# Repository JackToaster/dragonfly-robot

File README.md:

# Dragonfly Robot
This repository contains hardware and firmware files for a flight controller & 4-channel servo driver, intended for my dragonfly ornithopter robot.

## Robot hardware
The robot is built from components 3d printed out of lightweight PLA and pulltruded carbon fiber rods, with two standard 3.7g RC servos actuating each wing.

## PCB
The flight controlelr hardware is based on the WCH CH32V203, a low-cost RISC-V microcontroller.
Motor drives use the TI DRV8212 full-bridge driver and INA199 current sense amplifier for current feedback.
Each controller drives one pair of wings (four actuators). The controllers for each wing pair communicate with each other via I2C. An I2C IMU (MPU6050/MPU9250) is used for attitude control, and an RC receiver is connected over a serial link via the CRSF protocol.

## Firmware
The firmware in this repository utilizes CNLohr's [CH32Fun](https://github.com/cnlohr/ch32fun) framework for register mapping and hardware initialization functionality.

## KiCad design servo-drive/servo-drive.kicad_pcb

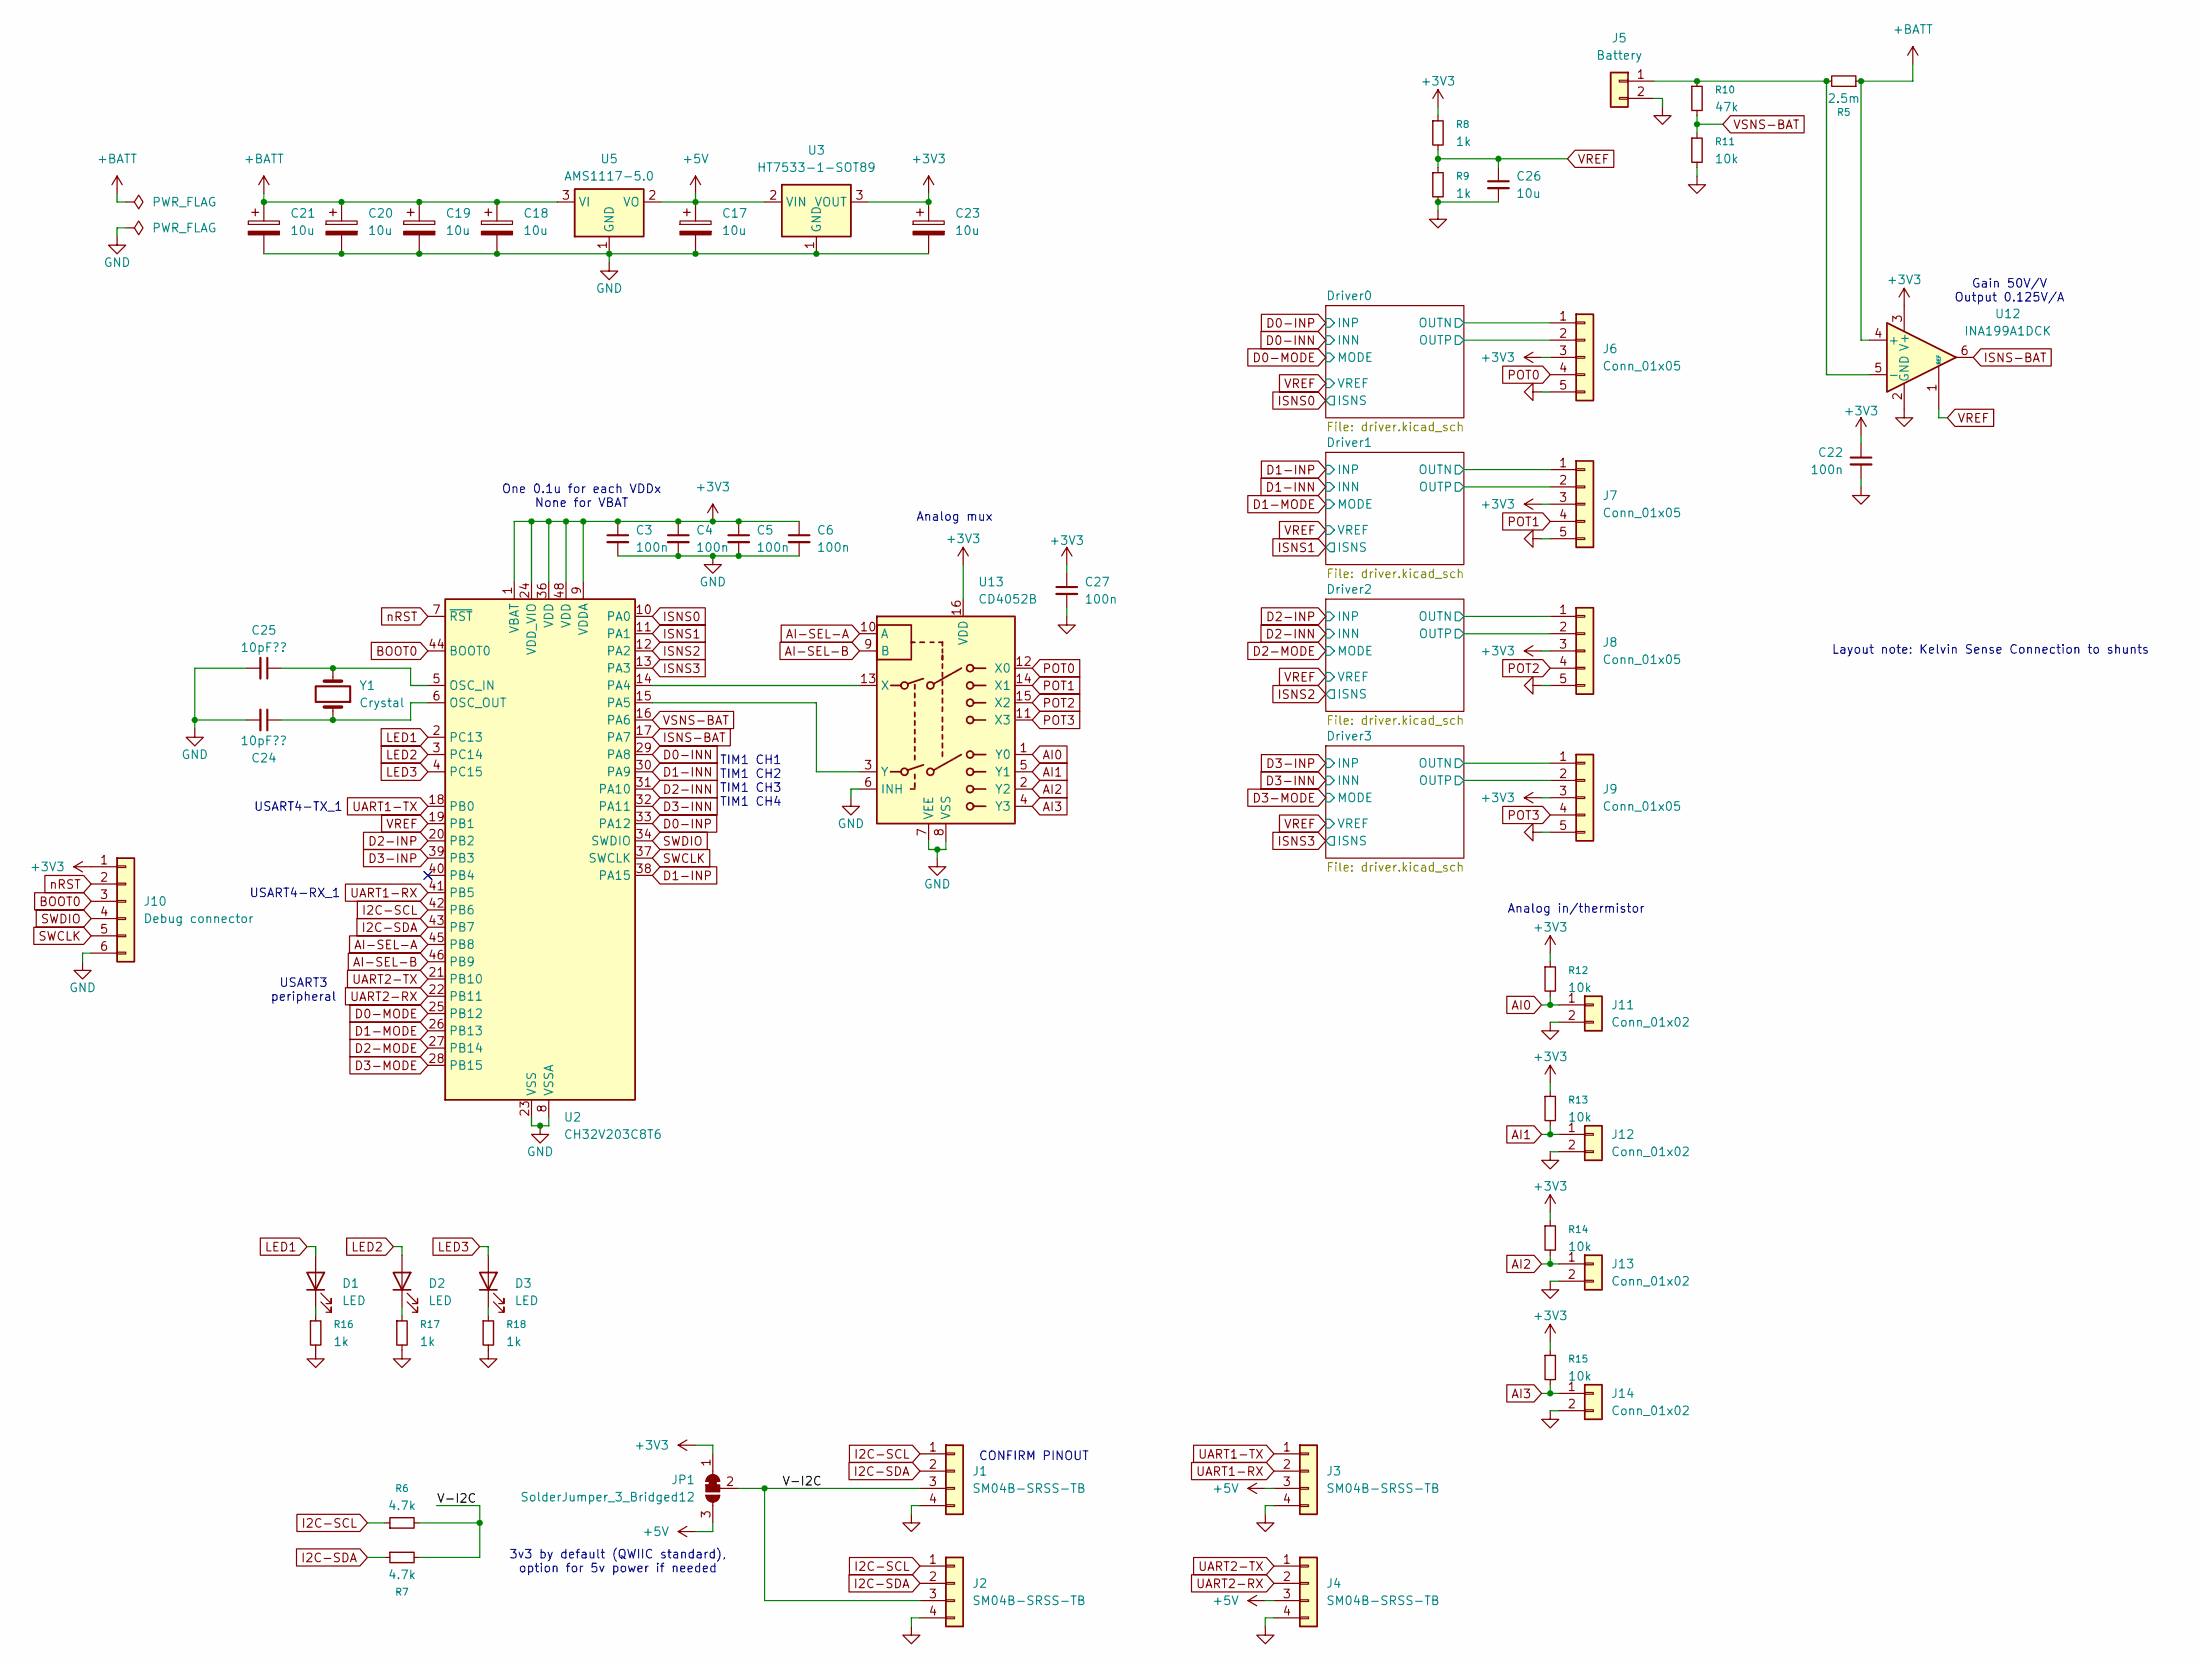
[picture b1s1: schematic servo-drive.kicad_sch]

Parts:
C3, C4, C5, C6, C22, C27: 100n; C_0402_1005Metric; LCSC C307331
C17, C18, C19, C20, C21, C23: 10u; CP_EIA-3216-18_Kemet-A; LCSC C7171
C24, C25: 10pF??; C_0402_1005Metric; LCSC C32949
C26: 10u; C_0603_1608Metric; LCSC C19702
D1, D2, D3: LED; LED_0603_1608Metric_Pad1.05x0.95mm_HandSolder
J1, J2, J3, J4: SM04B-SRSS-TB; JST_ZH_B4B-ZR_1x04_P1.50mm_Vertical
J5: Battery; SolderWire-1sqmm_1x02_P7.8mm_D1.4mm_OD3.9mm
J6, J7, J8, J9: Conn_01x05; JST_ZH_B5B-ZR_1x05_P1.50mm_Vertical
J10: Debug connector; PinHeader_1x06_P1.27mm_Vertical
J11, J12, J13, J14: Conn_01x02; JST_ZH_B2B-ZR_1x02_P1.50mm_Vertical
JP1: SolderJumper_3_Bridged12; SolderJumper-3_P1.3mm_Bridged12_RoundedPad1.0x1.5mm
R5: 2.5m; R_0805_2012Metric; LCSC C728266
R6, R7: 4.7k; R_0402_1005Metric; LCSC C25900
R8, R9, R16, R17, R18: 1k; R_0402_1005Metric; LCSC C11702
R10: 47k; R_0402_1005Metric; LCSC C25792
R11, R12, R13, R14, R15: 10k; R_0402_1005Metric; LCSC C25744
U2: CH32V203C8T6; LQFP-48_7x7mm_P0.5mm; LCSC C3001172
U3: HT7533-1-SOT89; SOT-89-3; LCSC C14289
U5: AMS1117-5.0; SOT-223-3_TabPin2; LCSC C6187
U12: INA199A1DCK; SOT-363_SC-70-6; LCSC C2653849
U13: CD4052B; SOIC-16_3.9x9.9mm_P1.27mm; LCSC C6521
Y1: Crystal; Crystal_SMD_5032-2Pin_5.0x3.2mm; LCSC C115962

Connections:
+3V3: C3.1, C4.1, C5.1, C6.1, C22.1, C23.1, C27.1, J6.3, J7.3, J8.3, J9.3, J10.1, JP1.1 (A), R8.1, R12.1, R13.1, R14.1, R15.1, U2.1 (VBAT), U2.9 (VDDA), U2.24 (VDD_VIO), U2.36 (VDD), U2.48 (VDD), U3.3 (VOUT), U12.3 (V+), U13.16 (VDD); also elsewhere on the board
+5V: C17.1, J3.3, J4.3, JP1.3 (B), U3.2 (VIN), U5.2 (VO)
+BATT: C18.1, C19.1, C20.1, C21.1, R5.1, U5.3 (VI), U12.4 (+); also elsewhere on the board
/Driver0/OUTN: J6.1; also elsewhere on the board
/Driver0/OUTP: J6.2; also elsewhere on the board
/Driver1/OUTN: J7.1; also elsewhere on the board
/Driver1/OUTP: J7.2; also elsewhere on the board
/Driver2/OUTN: J8.1; also elsewhere on the board
/Driver2/OUTP: J8.2; also elsewhere on the board
/Driver3/OUTN: J9.1; also elsewhere on the board
/Driver3/OUTP: J9.2; also elsewhere on the board
/V-I2C: J1.3, J2.3, JP1.2 (C), R6.2, R7.2
AI0: J11.1, R12.2, U13.1 (Y0)
AI1: J12.1, R13.2, U13.5 (Y1)
AI2: J13.1, R14.2, U13.2 (Y2)
AI3: J14.1, R15.2, U13.4 (Y3)
AI-SEL-A: U2.45 (PB8), U13.10 (A)
AI-SEL-B: U2.46 (PB9), U13.9 (B)
BOOT0: J10.3, U2.44 (BOOT0)
D0-INN: U2.29 (PA8); also elsewhere on the board
D0-INP: U2.33 (PA12); also elsewhere on the board
D0-MODE: U2.25 (PB12); also elsewhere on the board
D1-INN: U2.30 (PA9); also elsewhere on the board
D1-INP: U2.38 (PA15); also elsewhere on the board
D1-MODE: U2.26 (PB13); also elsewhere on the board
D2-INN: U2.31 (PA10); also elsewhere on the board
D2-INP: U2.20 (PB2); also elsewhere on the board
D2-MODE: U2.27 (PB14); also elsewhere on the board
D3-INN: U2.32 (PA11); also elsewhere on the board
D3-INP: U2.39 (PB3); also elsewhere on the board
D3-MODE: U2.28 (PB15); also elsewhere on the board
GND: C3.2, C4.2, C5.2, C6.2, C17.2, C18.2, C19.2, C20.2, C21.2, C22.2, C23.2, C24.2, C25.2, C26.2, C27.2, J1.4, J2.4, J3.4, J4.4, J5.2, J6.5, J7.5, J8.5, J9.5, J10.6, J11.2, J12.2, J13.2, J14.2, R9.2, R11.2, R16.2, R17.2, R18.2, U2.8 (VSSA), U2.23 (VSS), U2.35 (VSS), U2.47 (VSS), U3.1 (GND), U5.1 (GND), U12.2 (GND), U13.6 (INH), U13.7 (VEE), U13.8 (VSS); also elsewhere on the board
I2C-SCL: J1.1, J2.1, R6.1, U2.42 (PB6)
I2C-SDA: J1.2, J2.2, R7.1, U2.43 (PB7)
ISNS0: U2.10 (PA0); also elsewhere on the board
ISNS1: U2.11 (PA1); also elsewhere on the board
ISNS2: U2.12 (PA2); also elsewhere on the board
ISNS3: U2.13 (PA3); also elsewhere on the board
ISNS-BAT: U2.17 (PA7), U12.6
LED1: D1.2 (A), U2.2 (PC13)
LED2: D2.2 (A), U2.3 (PC14)
LED3: D3.2 (A), U2.4 (PC15)
unnamed: D1.1 (K), R16.1
unnamed: D2.1 (K), R17.1
unnamed: D3.1 (K), R18.1
unnamed: J5.1, R5.2, R10.1, U12.5 (-)
unnamed: C25.1, U2.5 (OSC_IN), Y1.2
unnamed: C24.1, U2.6 (OSC_OUT), Y1.1
unnamed: U2.14 (PA4), U13.13 (X)
unnamed: U2.15 (PA5), U13.3 (Y)
POT0: J6.4, U13.12 (X0)
POT1: J7.4, U13.14 (X1)
POT2: J8.4, U13.15 (X2)
POT3: J9.4, U13.11 (X3)
SWCLK: J10.5, U2.37 (SWCLK)
SWDIO: J10.4, U2.34 (SWDIO)
UART1-RX: J3.2, U2.41 (PB5)
UART1-TX: J3.1, U2.18 (PB0)
UART2-RX: J4.2, U2.22 (PB11)
UART2-TX: J4.1, U2.21 (PB10)
VREF: C26.1, R8.2, R9.1, U2.19 (PB1), U12.1 (REF); also elsewhere on the board
VSNS-BAT: R10.2, R11.1, U2.16 (PA6)
nRST: J10.2, U2.7 (~RST)

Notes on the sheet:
Analog mux
USART4-TX_1
Analog in/thermistor
USART4-RX_1
Gain 50V/V Output 0.125V/A
Layout note: Kelvin Sense Connection to shunts
CONFIRM PINOUT
One 0.1u for each VDDx None for VBAT
3v3 by default (QWIIC standard), option for 5v power if needed
USART3 peripheral
TIM1 CH1 TIM1 CH2 TIM1 CH3 TIM1 CH4

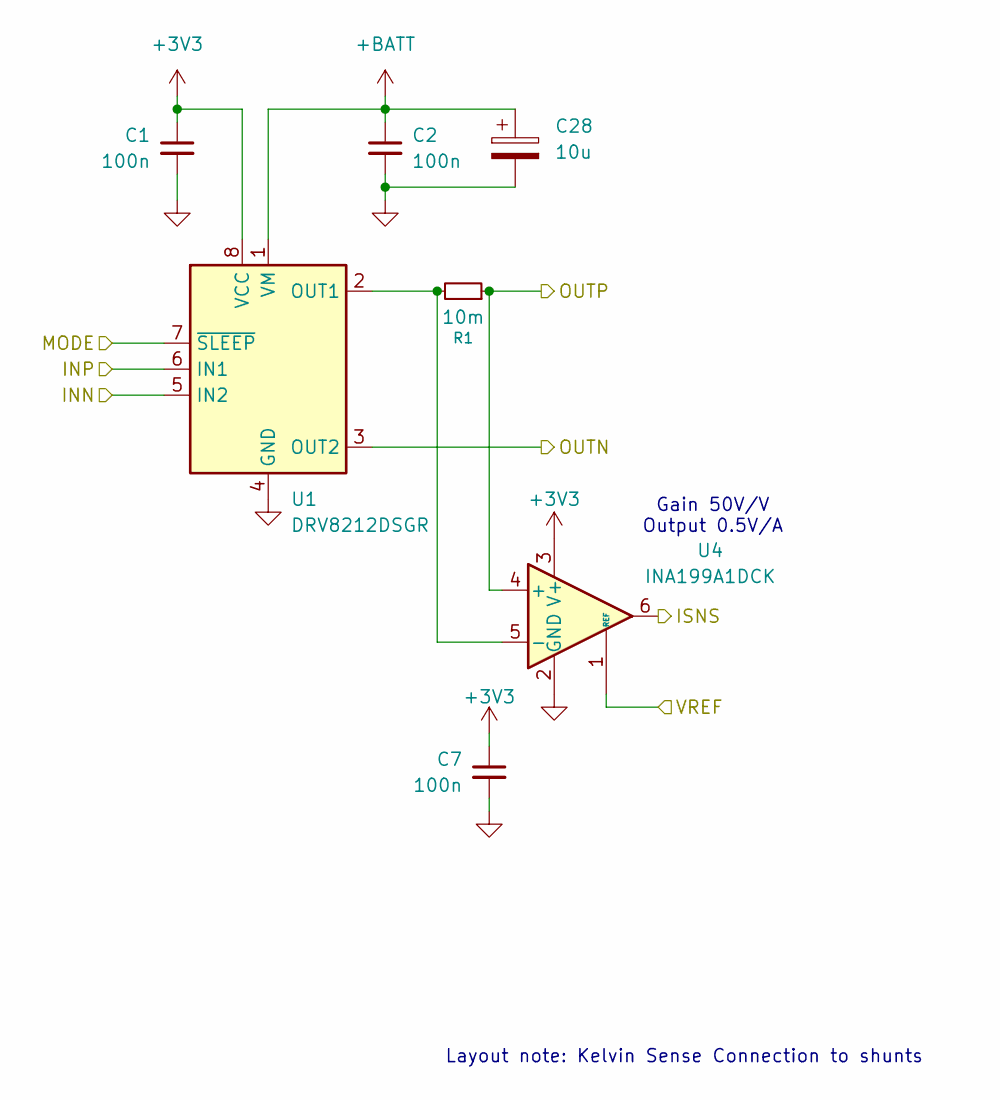
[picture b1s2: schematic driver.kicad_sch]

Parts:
C1, C2, C7: 100n; C_0402_1005Metric; LCSC C307331
C28: 10u; CP_EIA-3216-18_Kemet-A; LCSC C7171
R1: 10m; R_0805_2012Metric; LCSC C104574
U1: DRV8212DSGR; WSON-8-1EP_2x2mm_P0.5mm_EP0.9x1.6mm_ThermalVias; LCSC C2843766
U4: INA199A1DCK; SOT-363_SC-70-6; LCSC C2653849

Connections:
+3V3: C1.1, C7.1, U1.8 (VCC), U4.3 (V+); also elsewhere on the board
+BATT: C2.1, C28.1, U1.1 (VM); also elsewhere on the board
/Driver0/OUTN: U1.3 (OUT2); also elsewhere on the board
/Driver0/OUTP: R1.1, U4.4 (+); also elsewhere on the board
D0-INN: U1.5 (IN2); also elsewhere on the board
D0-INP: U1.6 (IN1); also elsewhere on the board
D0-MODE: U1.7 (~SLEEP); also elsewhere on the board
GND: C1.2, C2.2, C7.2, C28.2, U1.4 (GND), U1.9 (GND), U4.2 (GND); also elsewhere on the board
ISNS0: U4.6; also elsewhere on the board
unnamed: R1.2, U1.2 (OUT1), U4.5 (-)
VREF: U4.1 (REF); also elsewhere on the board

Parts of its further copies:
C8, C9, C10, C11, C12, C13, C14, C15, C16: 100n; C_0402_1005Metric; LCSC C307331
C29, C30, C31: 10u; CP_EIA-3216-18_Kemet-A; LCSC C7171
R2, R3, R4: 10m; R_0805_2012Metric; LCSC C104574
U6, U8, U10: DRV8212DSGR; WSON-8-1EP_2x2mm_P0.5mm_EP0.9x1.6mm_ThermalVias; LCSC C2843766
U7, U9, U11: INA199A1DCK; SOT-363_SC-70-6; LCSC C2653849

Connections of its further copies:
+3V3: C8.1, C10.1, C11.1, C13.1, C14.1, C16.1, U6.8 (VCC), U7.3 (V+), U8.8 (VCC), U9.3 (V+), U10.8 (VCC), U11.3 (V+); also elsewhere on the board
+BATT: C9.1, C12.1, C15.1, C29.1, C30.1, C31.1, U6.1 (VM), U8.1 (VM), U10.1 (VM); also elsewhere on the board
/Driver1/OUTN: U6.3 (OUT2); also elsewhere on the board
/Driver1/OUTP: R2.1, U7.4 (+); also elsewhere on the board
/Driver2/OUTN: U8.3 (OUT2); also elsewhere on the board
/Driver2/OUTP: R3.1, U9.4 (+); also elsewhere on the board
/Driver3/OUTN: U10.3 (OUT2); also elsewhere on the board
/Driver3/OUTP: R4.1, U11.4 (+); also elsewhere on the board
D1-INN: U6.5 (IN2); also elsewhere on the board
D1-INP: U6.6 (IN1); also elsewhere on the board
D1-MODE: U6.7 (~SLEEP); also elsewhere on the board
D2-INN: U8.5 (IN2); also elsewhere on the board
D2-INP: U8.6 (IN1); also elsewhere on the board
D2-MODE: U8.7 (~SLEEP); also elsewhere on the board
D3-INN: U10.5 (IN2); also elsewhere on the board
D3-INP: U10.6 (IN1); also elsewhere on the board
D3-MODE: U10.7 (~SLEEP); also elsewhere on the board
GND: C8.2, C9.2, C10.2, C11.2, C12.2, C13.2, C14.2, C15.2, C16.2, C29.2, C30.2, C31.2, U6.4 (GND), U6.9 (GND), U7.2 (GND), U8.4 (GND), U8.9 (GND), U9.2 (GND), U10.4 (GND), U10.9 (GND), U11.2 (GND); also elsewhere on the board
ISNS1: U7.6; also elsewhere on the board
ISNS2: U9.6; also elsewhere on the board
ISNS3: U11.6; also elsewhere on the board
unnamed: R2.2, U6.2 (OUT1), U7.5 (-)
unnamed: R3.2, U8.2 (OUT1), U9.5 (-)
unnamed: R4.2, U10.2 (OUT1), U11.5 (-)
VREF: U7.1 (REF), U9.1 (REF), U11.1 (REF); also elsewhere on the board

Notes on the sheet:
Gain 50V/V Output 0.5V/A
Layout note: Kelvin Sense Connection to shunts

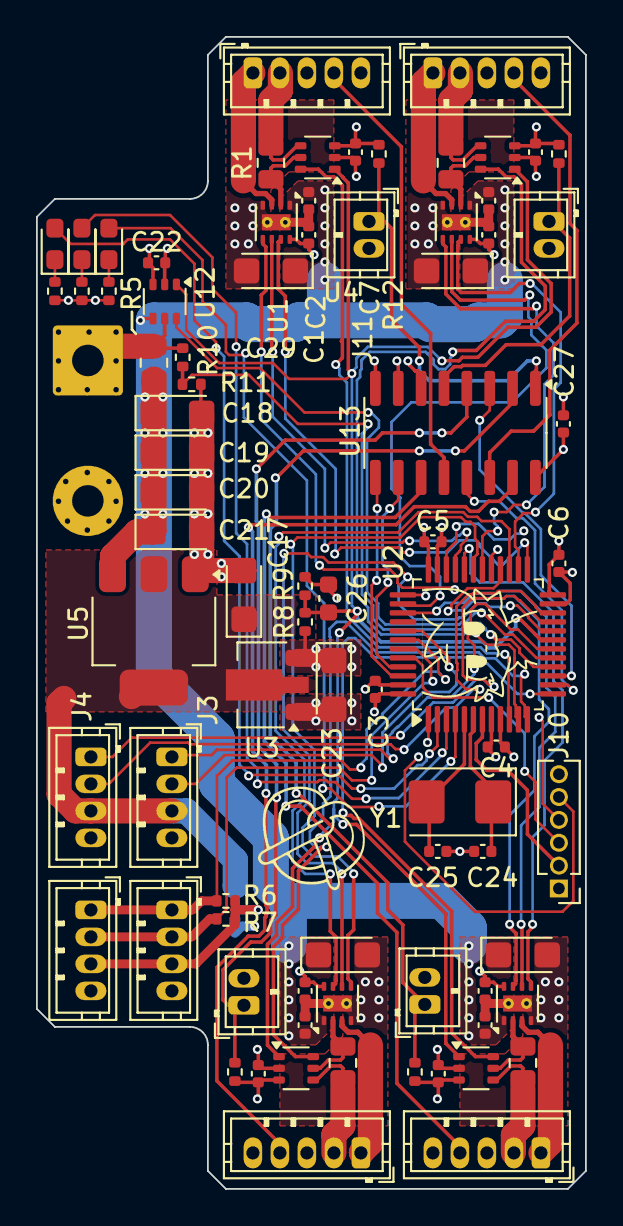
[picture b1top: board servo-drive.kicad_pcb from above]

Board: 4 copper layers, 30.5 x 64.0 mm, 81 parts (1 on the bottom side), 67 nets.

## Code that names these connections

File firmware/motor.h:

#pragma once
#include "ch32fun.h"
#include "ch32v20xhw.h"

#define CURRENT_FEEDBACK_INVERTED

#define MOTOR_CURRENT_GAIN 1700 // uA per ADC count, divide by 1000. Theoretically 1.611 but calibrated to 1.7

#define MOTOR_MAX_CURRENT_mA 200
#define MOTOR_DUTY_MAX 14400 // sets 20kHz PWM frequency
#define MOTOR_DUTY_MIN 600 // can't go below this or the motors fall alseep :P

#define CURRENT_GAIN_SCALE 32768 // Gains are 1/8192 of full duty per unit
#define CURRENT_kP 1
#define CURRENT_kI 500

#define MOTOR_KV 2750 // units/sec/V

#define POSITION_GAIN_SCALE 32768
#define POSITION_kP 50
#define POSITION_kI 0
#define POSITION_kD 0

#define MOTOR_D0_MODE PB12
#define MOTOR_D1_MODE PB13
#define MOTOR_D2_MODE PB14
#define MOTOR_D3_MODE PB15

#define MOTOR_D0_DIR PA12
#define MOTOR_D1_DIR PA15
#define MOTOR_D2_DIR PB2
#define MOTOR_D3_DIR PB3

#define MOTOR_D0_EN PA8
#define MOTOR_D1_EN PA9
#define MOTOR_D2_EN PA10
#define MOTOR_D3_EN PA11

#define N_MOTORS 4

typedef enum MotorControlMode {
	MOTOR_DISABLED=0,
	MOTOR_DUTY_CYCLE=1,
	MOTOR_CURRENT_CONTROL=2,
	MOTOR_POSITION_CONTROL=3,
} MotorControlMode;

typedef struct MotorCtrlT {
	MotorControlMode mode;

	uint32_t duty_cap;
	int32_t duty; // -MOTOR_DUTY_MAX to +MOTOR_DUTY_MAX
	volatile uint16_t* duty_buffer; // Buffer to write PWM duty
	uint32_t dir_pin;

	int32_t current_setpoint; // motor current setpoint in ADC counts
	int32_t current_integrator; // integrator for current control loop

	int32_t position_setpoint; // in motor sensor units
	int32_t position_integrator; // integrator for current control loop
	int32_t feedforward_vel; // motor sensor units/sec
	int32_t prev_pos_err;

} MotorCtrlT;

void set_duty_pct(MotorCtrlT* motor, int32_t duty_pct);

void set_current_mA(MotorCtrlT* motor, int32_t current_mA);

void set_position(MotorCtrlT* motor, int32_t setpoint);

extern MotorCtrlT motors[N_MOTORS];

void motor_init( void );

void wakeup_motors( void );

void motor_update( void );

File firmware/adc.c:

#include "adc.h"
#include "ch32fun.h"
#include "ch32v20xhw.h"


// ADC
ADCStateT adc_state;


void init_adc_in_pin(GPIO_TypeDef *gpio, uint32_t pin) {
	gpio->CFGLR &= ~(0xf << (4 * pin)); // CNF = 00: Analog, MODE = 00: Input
}

void adc_dma_init( void ) {
	// DMA Config
    // Start DMA clock
    RCC->AHBPCENR |= RCC_AHBPeriph_DMA1;
    Delay_Us(100);
    // Setup DMA Channel 1 (adc triggered) as reading, 16-bit, linear buffer
    DMA1_Channel1->CFGR = DMA_DIR_PeripheralSRC |
						  DMA_PeripheralInc_Disable |
                          DMA_MemoryInc_Enable |
                          DMA_PeripheralDataSize_HalfWord |
                          DMA_MemoryDataSize_HalfWord |
						  DMA_Mode_Normal |
                          DMA_M2M_Disable;
    

    // No of samples to get before irq
    DMA1_Channel1->CNTR = ADC_CHANNELS;
    // Source
    DMA1_Channel1->PADDR = (uint32_t)&ADC1->RDATAR;
    // Destination
    DMA1_Channel1->MADDR = (uint32_t)(adc_state.buffer);

    // Enable IRQ and DMA channel
    NVIC_EnableIRQ(DMA1_Channel1_IRQn);
    DMA1_Channel1->CFGR |= DMA_IT_TC ;

}

void adc_init( void )
{    
	// Enable IRQ and DMA channel
    NVIC_EnableIRQ(DMA1_Channel1_IRQn);
    DMA1_Channel1->CFGR |= DMA_IT_TC | DMA_CFGR1_EN;

	// ADCCLK = 12 MHz (SYSCLK=72MHz, divide by 6)
    RCC->CFGR0 &= ~RCC_ADCPRE;
    RCC->CFGR0 |= RCC_ADCPRE_DIV6;
    
    // Enable GPIOA and ADC
    RCC->APB2PCENR |= RCC_APB2Periph_GPIOA | RCC_APB2Periph_ADC1;
    
	funPinMode(PA0, GPIO_CFGLR_IN_ANALOG);
	funPinMode(PA1, GPIO_CFGLR_IN_ANALOG);
	funPinMode(PA2, GPIO_CFGLR_IN_ANALOG);
	funPinMode(PA3, GPIO_CFGLR_IN_ANALOG);
	funPinMode(PA4, GPIO_CFGLR_IN_ANALOG);
	funPinMode(PA5, GPIO_CFGLR_IN_ANALOG);
	funPinMode(PA6, GPIO_CFGLR_IN_ANALOG);
	funPinMode(PA7, GPIO_CFGLR_IN_ANALOG);

	funPinMode(PB1, GPIO_CFGLR_IN_ANALOG); // ADC IN9

    // Reset the ADC to init all regs
    RCC->APB2PRSTR |= RCC_APB2Periph_ADC1;
    RCC->APB2PRSTR &= ~RCC_APB2Periph_ADC1;
    
    // Set up conversions
	ADC1->RSQR1 = ((ADC_CHANNELS - 1) << 20); // number of channels converted
	ADC1->RSQR2 = (6 << 0) | (7 << 5) | (9 << 10); // inputs 6-8
	ADC1->RSQR3 = (0 << 0) | (1 << 5) | (2 << 10) | (3 << 15) | (4 << 20) | (5 << 25);	// inputs 0-5
    
    // set sampling time for channels???
    ADC1->SAMPTR2 = ADC_SampleTime_239Cycles5 | (ADC_SampleTime_239Cycles5 << 3)  | (ADC_SampleTime_239Cycles5 << 6)  | 
		    (ADC_SampleTime_239Cycles5 << 9)  | (ADC_SampleTime_239Cycles5 << 12) | (ADC_SampleTime_239Cycles5 << 15) |
			(ADC_SampleTime_239Cycles5 << 18) | (ADC_SampleTime_239Cycles5 << 21) | (ADC_SampleTime_239Cycles5 << 24); 
			
    // turn on ADC and set rule group to sw trig
    ADC1->CTLR2 |= ADC_ADON | ADC_EXTSEL | ADC_EXTTRIG ;
	ADC1->CTLR1 |= ADC_SCAN; // scan mode, measure all channels at once
    
    // Reset calibration
    ADC1->CTLR2 |= ADC_RSTCAL;
    while(ADC1->CTLR2 & ADC_RSTCAL);
    
    // Calibrate
    ADC1->CTLR2 |= ADC_CAL;
    while(ADC1->CTLR2 & ADC_CAL){}


	adc_dma_init();

	// should be ready for SW conversion now
}

volatile uint8_t adc_dma_running = 0;
void adc_poll_dma( void )
{
	// wait if necessary
	while(adc_dma_running == 1);

	
	adc_dma_running = 1;

	// If TIM1 is running (Motor PWM), wait until it resets to get consistent readings (Always sample at the same time relative to PWM)
	if(TIM1->CTLR1 & TIM_CEN) {
		volatile uint16_t cnt = TIM1->CNT;
		// wait for rollover
		while(TIM1->CNT >= cnt) {
			cnt = TIM1->CNT;
		}
	}
	
	__disable_irq();
	// Scan
    ADC1->CTLR1 |= ADC_SCAN ;
	ADC1->CTLR2 |= ADC_DMA ;
	
    // enable dma
	DMA1_Channel1->CFGR |= DMA_CFGR1_EN;
	
	// start sw conversion (auto clears)
	ADC1->CTLR2 |= ADC_SWSTART;
	__enable_irq();
}

void adc_wait_for_data( void ) {
	while(adc_dma_running);
	return;
}

void adc_process_data() {
	adc_state.pot[adc_state.selected_ai] = adc_state.buffer[ADC_BUFFER_POT];
	adc_state.temp_ai[adc_state.selected_ai] = adc_state.buffer[ADC_BUFFER_AI_TEMP];
	uint16_t vref = adc_state.buffer[ADC_BUFFER_VREF];
	adc_state.vref = vref;

	adc_state.isns_motor[0] = (int32_t)adc_state.buffer[ADC_BUFFER_ISNS0] - (int32_t)vref;
	adc_state.isns_motor[1] = (int32_t)adc_state.buffer[ADC_BUFFER_ISNS1] - (int32_t)vref;
	adc_state.isns_motor[2] = (int32_t)adc_state.buffer[ADC_BUFFER_ISNS2] - (int32_t)vref;
	adc_state.isns_motor[3] = (int32_t)adc_state.buffer[ADC_BUFFER_ISNS3] - (int32_t)vref;

	adc_state.vsns_bat = adc_state.buffer[ADC_BUFFER_VSNS_BAT];
	adc_state.isns_bat = (int32_t)adc_state.buffer[ADC_BUFFER_ISNS_BAT] - (int32_t)vref;

}

void DMA1_Channel1_IRQHandler()
{
    if(DMA1->INTFR & DMA1_FLAG_TC1) {
        DMA1->INTFCR = DMA_CTCIF1;
        adc_dma_init();
		adc_dma_running = 0;
    }
}

void adc_ai_select(uint8_t input) {
	if(input >= 4) {
		printf("Invalid analog input selection: %d\n", input);
		return;
	}
	funDigitalWrite(AI_SEL_A, (input & 1) != 0);
	funDigitalWrite(AI_SEL_B, (input & 2) != 0);
	adc_state.selected_ai = input;
	Delay_Us(1); // let it settle for a microsecond before sampling
}

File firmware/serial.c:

#include "serial.h"
#include "ch32fun.h"
#include "ch32v20xhw.h"


void serial_init() {
	// USART3

	// Enable UART (GPIOB already enabled)
	RCC->APB1PCENR |= RCC_APB1Periph_USART3;

	// Push-Pull, 10MHz Output on D5, with AutoFunction
	funPinMode(PB10, GPIO_CFGLR_OUT_10Mhz_AF_PP); // USART3-TX
	funPinMode(PB11, GPIO_CFGLR_IN_FLOAT); // USART3-RX

	// Setup UART for Tx 8n1
	USART3->CTLR1 = USART_WordLength_8b | USART_Parity_No | USART_Mode_Tx | USART_Mode_Rx | USART_FLAG_RXNE;
	USART3->CTLR2 = USART_StopBits_1 | USART_HardwareFlowControl_None;
	// Enable Tx DMA event
	USART3->CTLR3 = USART_DMAReq_Tx ;

	// Set baud rate and enable UART
	USART3->BRR = ((FUNCONF_SYSTEM_CORE_CLOCK)/2 + (UART_BR)/2) / (UART_BR);
	USART3->CTLR1 |= CTLR1_UE_Set;

	NVIC_EnableIRQ(USART3_IRQn);

	// USART4
	// TODO This breaks ADC for some reason!!!
	// Enable UART and GPIOD
	// RCC->APB1PCENR |= RCC_APB1Periph_UART4; // UART4 is actually a USART on v203

	// // Push-Pull, 10MHz Output on D5, with AutoFunction
	// AFIO->PCFR2 |= GPIO_FullRemap_USART4;
	// funPinMode(PB0, GPIO_CFGLR_OUT_50Mhz_AF_PP); // USART3-TX
	// funPinMode(PB5, GPIO_CFGLR_IN_FLOAT); // USART3-RX

	// // Setup UART for Tx 8n1
	// UART4->CTLR1 = USART_WordLength_8b | USART_Parity_No | USART_Mode_Tx;
	// UART4->CTLR2 = USART_StopBits_1;
	// // Enable Tx DMA event
	// UART4->CTLR3 = USART_DMAReq_Tx;

	// // Set baud rate and enable UART
	// UART4->BRR = ((FUNCONF_SYSTEM_CORE_CLOCK / 2) + (UART_BR)/2) / (UART_BR);
	// UART4->CTLR1 |= CTLR1_UE_Set;
}

void dma_uart_setup(void)
{
	// Enable DMA peripheral
	RCC->AHBPCENR |= RCC_AHBPeriph_SRAM | RCC_AHBPeriph_DMA1;

	// Disable channel just in case there is a transfer in progress
	DMA1_Channel2->CFGR &= ~DMA_CFGR1_EN;

	// USART3 TX uses DMA channel 2
	DMA1_Channel2->PADDR = (uint32_t)&USART3->DATAR;
	// MEM2MEM: 0 (memory to peripheral)
	// PL: 0 (low priority since UART is a relatively slow peripheral)
	// MSIZE/PSIZE: 0 (8-bit)
	// MINC: 1 (increase memory address)
	// CIRC: 0 (one shot)
	// DIR: 1 (read from memory)
	// TEIE: 0 (no tx error interrupt)
	// HTIE: 0 (no half tx interrupt)
	// TCIE: 1 (transmission complete interrupt enable)
	// EN: 0 (do not enable DMA yet)
	DMA1_Channel2->CFGR = DMA_CFGR1_MINC | DMA_CFGR1_DIR | DMA_CFGR1_TCIE | DMA_Priority_VeryHigh;

	// Enable channel 4 interrupts
	NVIC_EnableIRQ(DMA1_Channel2_IRQn);
}

// DMA transfer completion interrupt. It will fire when the DMA transfer is
// complete. We use it just to blink the LED
__attribute__((interrupt)) __attribute__((section(".srodata")))
void DMA1_Channel2_IRQHandler(void)
{
	// Clear flag
	DMA1->INTFCR |= DMA_CTCIF2;
}

void dma_uart_tx(const void *data, uint32_t len)
{
	// Disable DMA channel (just in case a transfer is pending)
	DMA1_Channel2->CFGR &= ~DMA_CFGR1_EN;
	// Set transfer length and source address
	DMA1_Channel2->CNTR = len;
	DMA1_Channel2->MADDR = (uint32_t)data;
	// Enable DMA channel to start the transfer
	DMA1_Channel2->CFGR |= DMA_CFGR1_EN;
}


UartRxBufferT uart3_rxbuf;
// UART3 RXNE Interrupt
__attribute__((interrupt)) __attribute__((section(".srodata")))
void USART3_IRQHandler(void)
{
	// copy to buffer
	uart3_rxbuf.buffer[uart3_rxbuf.write_addr] = (uint8_t) (USART3->DATAR & (uint16_t)0x01FF);
	uart3_rxbuf.write_addr = (uart3_rxbuf.write_addr + 1) % UART_RX_BUF_SIZE;



	uart3_rxbuf.overrun |= uart3_rxbuf.write_addr == uart3_rxbuf.read_addr;

	// Clear flag
	USART3->STATR &= ~USART_FLAG_RXNE;
}


void clear_buf(UartRxBufferT *buf) {
	buf->overrun = 0;
	buf->read_addr = buf->write_addr;
}

uint32_t bytes_available(UartRxBufferT* buf) {
	if(buf->overrun) {
		clear_buf(buf);
	}
	return (buf->write_addr + UART_RX_BUF_SIZE - buf->read_addr) % UART_RX_BUF_SIZE;
}

// return pointer to a contiguous buffer of data, null terminated
uint8_t* read_data(UartRxBufferT* buf, uint32_t len) { // todo maybe pass a destination pointer like memcpy does?
	uint32_t end_addr = (buf->read_addr + len) % UART_RX_BUF_SIZE;
	uint8_t* write_ptr = buf->b2;
	// we do a fun lil bespoke memcpy
	for(;buf->read_addr != end_addr; buf->read_addr = (buf->read_addr + 1) % UART_RX_BUF_SIZE) {
		*write_ptr++ = buf->buffer[buf->read_addr];
	}
	*write_ptr = 0; // null term
	return buf->b2;
}

uint8_t peek(UartRxBufferT* buf) { // look at first byte of buffer, but don't advance read pointer
	return buf->buffer[buf->read_addr];
}
uint8_t* peek_n(UartRxBufferT* buf, uint32_t len) { // look at first bytes of buffer, but don't advance read pointer
	uint32_t end_addr = (buf->read_addr + len) % UART_RX_BUF_SIZE;
	uint8_t* write_ptr = buf->b2;

	uint32_t temp_read_addr = buf->read_addr;
	// we do a fun lil bespoke memcpy
	for(;temp_read_addr != end_addr; temp_read_addr = (temp_read_addr + 1) % UART_RX_BUF_SIZE) {
		*write_ptr++ = buf->buffer[temp_read_addr];
	}
	*write_ptr = 0; // null term
	return buf->b2;
}

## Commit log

2025-08-22 servo control
2025-08-28 serial working!
2025-09-01 start crsf/i2c dev
2025-09-02 add crc to crsf decoding, fix adc
2025-09-03 add images
